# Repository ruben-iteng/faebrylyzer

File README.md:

<div align="center">

# faebrylyzer

<br/>

8 channel logic analyser compatible with the fx2lafw firmware

</div>

## About

faebrylyzer is an 8 channel logic analyser compatible with the fx2lafw firmware. It is designed to be integrated as a module into other projects (e.g. a factory test rig).
This project is build with the open-source EDA [faebryk](https://github.com/faebryk/faebryk).

## Working with the source files

See [here](./docs/development.md) for the instructions on how to install and edit this project.

## Building

If you want to build the physical output of this project you can find the build instructions [here](./docs/build_instructions.md).

## Contributing

If you want to share your alterations, improvements, or add bugfixes to this project, please take a look at the [contributing guidelines](./docs/CONTRIBUTING.md).

## Community Support

Community support is provided via Discord; see the Resources below for details.

### Resources

- Source Code: [Github](https://github.com/ruben-iteng/faebrylyzer)
- Chat: Real-time chat happens in faebryk's Discord Server (chit-chat room for now). Use this Discord [Invite](https://discord.gg/95jYuPmnUW) to register
- Issues: [Issues](https://github.com/ruben-iteng/faebrylyzer/issues)

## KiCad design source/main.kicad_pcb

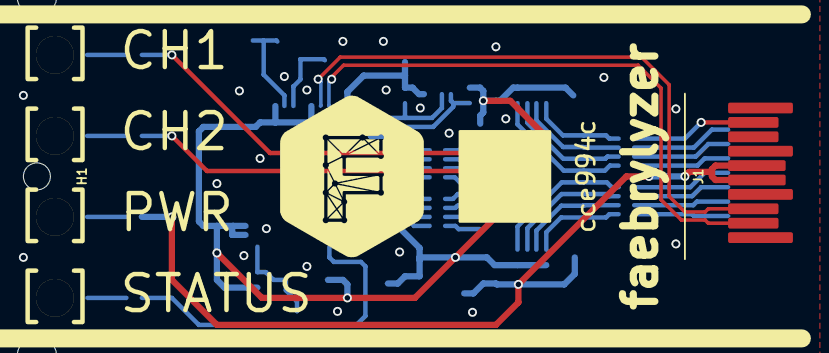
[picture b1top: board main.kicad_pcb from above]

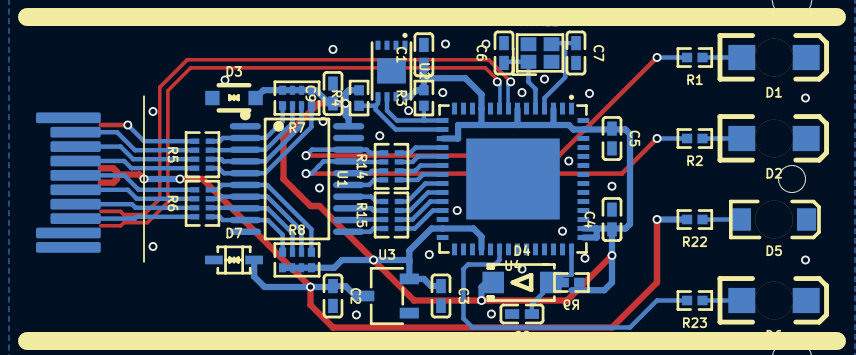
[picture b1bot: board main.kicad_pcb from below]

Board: 4 copper layers, 37 parts (34 on the bottom side), 47 nets.

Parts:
C1, C2, C3, C4, C5, C6, C7, C9: 15pF 50V C0G; C0402
C8: 1µF 25V X5R; C0402
D1, D2, D6: 3.05V; LED-SMD_L3.2-W1.3-RD_GREEN-MHT151UGCT
D3: SOD-323_L1.7-W1.3-LS2.5-BI
D4: 1.3V; SOD-123FL_L2.8-W1.8-LS3.7-RD
D5: 3.15V; LED-SMD_L3.2-W1.3-RD_MHT151WDT
D7: SOD-323_L1.8-W1.3-LS2.5-BI
H1: MountingSlot
J1: SFPEdgeConnector; SFP_Edge
LOGO1: faebrykLogo; faebryk_logo
R1, R2, R3, R4, R9: 100Ω; R0402
R5, R6, R14, R15: ResistorArray; RES-ARRAY-SMD_0402-8P-L2.0-W1.0-BL
R7, R8: ResistorArray; RES-ARRAY-SMD_8P-L2.0-W1.0-BL_CN24XXXX
R22: 1kΩ; R0402
R23: 200Ω; R0402
U1: SNx4LVC541A; TSSOP-20_L6.5-W4.4-P0.65-LS6.4-BL
U2: EEPROM; UDFN-8_L3.0-W2.0-P0.50-TL
U3: LDO 3.3V 237.5mA - 262.5mA Vin max 5V Iq; SOT-23-3_L2.9-W1.6-P1.90-LS2.8-BR
U4: CBM9002A_56ILG; QFN-56_L8.0-W8.0-P0.50-BL-EP
XTAL1: Crystal; CRYSTAL-SMD_4P-L2.0-W1.6-BL-A

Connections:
3v3: C1.1, C3.1, C4.1, C5.1, C9.1, D3.2, D4.1, R3.2, R4.2, R7.5, R7.6, R7.7, R7.8, R8.5, R8.6, R8.7, R8.8, R9.2, U1.20, U2.8, U3.2, U4.3, U4.7, U4.11, U4.17, U4.27, U4.32, U4.43, U4.44, U4.55
C6-1-U4-5-XTAL1-1: C6.1, U4.5, XTAL1.1
C7-1-U4-4-XTAL1-3: C7.1, U4.4, XTAL1.3
C8-1-D4-2-R9-1-U4-42: C8.1, D4.2, R9.1, U4.42
D1-2-R1-1: D1.2, R1.1
D2-2-R2-1: D2.2, R2.1
D5-2-R22-1: D5.2, R22.1
D6-2-R23-1: D6.2, R23.1
R23-2-U4-34: R23.2, U4.34
buffer_in_0: R5.5, R7.4, U1.2
buffer_in_1: R5.6, R7.3, U1.3
buffer_in_2: R5.7, R7.2, U1.4
buffer_in_3: R5.8, R7.1, U1.5
buffer_in_4: R6.5, R8.4, U1.6
buffer_in_5: R6.6, R8.3, U1.7
buffer_in_6: R6.7, R8.2, U1.8
buffer_in_7: R6.8, R8.1, U1.9
buffer_out_0: R1.2, R14.4, U1.18
buffer_out_1: R2.2, R14.3, U1.17
buffer_out_2: R14.2, U1.16
buffer_out_3: R14.1, U1.15
buffer_out_4: R15.4, U1.14
buffer_out_5: R15.3, U1.13
buffer_out_6: R15.2, U1.12
buffer_out_7: R15.1, U1.11
ch_0: J1.19, R5.4
ch_1: J1.2, R5.3
ch_2: J1.3, R5.2
ch_3: J1.4, R5.1
ch_4: J1.5, R6.4
ch_5: J1.6, R6.3
ch_6: J1.7, R6.2
ch_7: J1.8, R6.1
gnd: C1.2, C2.2, C3.2, C4.2, C5.2, C6.2, C7.2, C8.2, C9.2, D1.1, D2.1, D3.1, D5.1, D6.1, D7.1, J1.1, J1.10, J1.11, J1.14, J1.17, J1.20, U1.1, U1.10, U1.19, U2.1, U2.2, U2.3, U2.4, U2.7, U3.1, U4.6, U4.10, U4.12, U4.14, U4.26, U4.28, U4.41, U4.53, U4.56, U4.57, XTAL1.2, XTAL1.4
mcu_logic_0: R14.5, U4.18
mcu_logic_1: R14.6, U4.19
mcu_logic_2: R14.7, U4.20
mcu_logic_3: R14.8, U4.21
mcu_logic_4: R15.5, U4.22
mcu_logic_5: R15.6, U4.23
mcu_logic_6: R15.7, U4.24
mcu_logic_7: R15.8, U4.25
scl: R3.1, U2.6, U4.15
sda: R4.1, U2.5, U4.16
usb_N: J1.12, U4.9
usb_P: J1.13, U4.8
vbus: C2.1, D7.2, J1.15, J1.16, R22.2, U3.3

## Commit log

2024-07-10 Initialize repository
2024-08-03 Update readme with render placeholder
2024-08-23 initial version wip
2024-08-24 Add: routing and finilize placement
2024-08-24 Add: manufacturing arifacts
2024-08-25 Cleanup comments
2024-09-03 Update to fabll
2024-09-03 Update renders
2024-09-11 Fix some minor issues
2024-09-11 Fix constants; Run

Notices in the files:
README.md:
License: MIT
